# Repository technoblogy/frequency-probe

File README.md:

# Frequency Probe
A handheld tool that gives a visual indication of the frequency or voltage at the probe. See http://www.technoblogy.com/show?25C4

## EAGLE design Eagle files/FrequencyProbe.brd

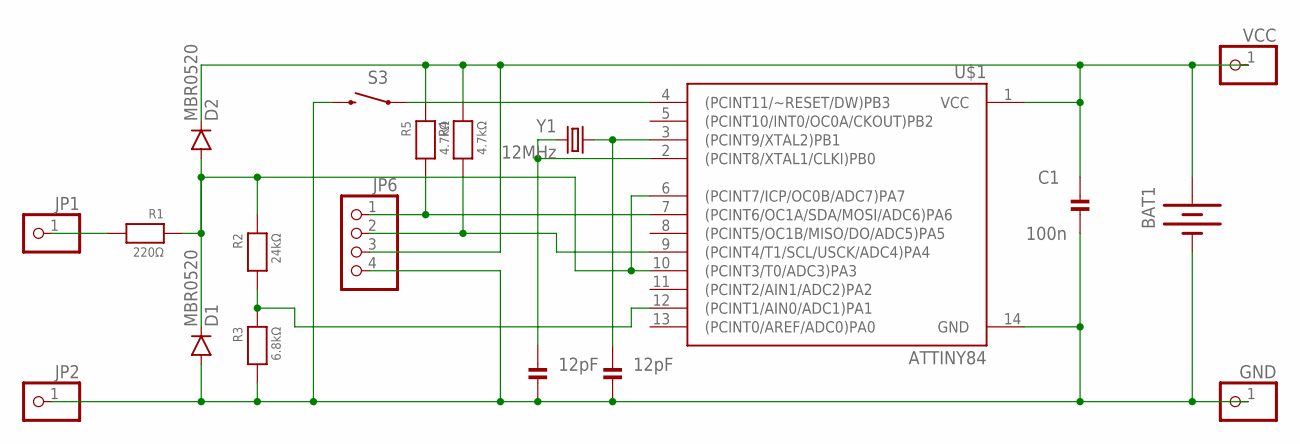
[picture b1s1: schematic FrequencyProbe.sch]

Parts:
BAT1: BATTERY12MM; BATTCON_12MM
C1: 100n; _0805MP
C12, C13: 12pF; _0805MP
D1, D2: MBR0520; SOD-123
GND: PINHD-1X1CB; 1X01-CLEANBIG
JP1, JP2: PINHD-1X1CB; 1X01-CLEANBIG
JP6: HEADER-1X4ROUND; 1X04_ROUND
R1: 220Ω; _0805MP
R2: 24kΩ; _0805MP
R3: 6.8kΩ; _0805MP
R4, R5: 4.7kΩ; _0805MP
S3: SWITCH-MOMENTARY-2SMD; TACTILE-SWITCH-SMD
U$1: ATTINY84; SO14
VCC: PINHD-1X1CB; 1X01-CLEANBIG
Y1: 12MHz; CRYSTAL-SMD-5X3

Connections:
GND: BAT1.GND (-), C1.2, C12.2, C13.2, D1.A, GND.1, JP2.1, JP6.4, R3.2, S3.3 (2), U$1.14 (GND)
unnamed: JP6.2, R4.2, U$1.9 ((PCINT4/T1/SCL/USCK/ADC4)PA4)
unnamed: JP6.1, R5.2, U$1.7 ((PCINT6/OC1A/SDA/MOSI/ADC6)PA6)
unnamed: D1.C, D2.A, R1.1, R2.1, U$1.6 ((PCINT7/ICP/OC0B/ADC7)PA7), U$1.10 ((PCINT3/T0/ADC3)PA3)
unnamed: C12.1, U$1.3 ((PCINT9/XTAL2)PB1), Y1.1
unnamed: S3.1, U$1.4 ((PCINT11/~RESET/DW)PB3)
unnamed: C13.1, U$1.2 ((PCINT8/XTAL1/CLKI)PB0), Y1.3 (2)
unnamed: R2.2, R3.1, U$1.12 ((PCINT1/AIN0/ADC1)PA1)
unnamed: JP1.1, R1.2
VCC: BAT1.PWR@1 (+), C1.1, D2.C, JP6.3, R4.1, R5.1, U$1.1 (VCC), VCC.1

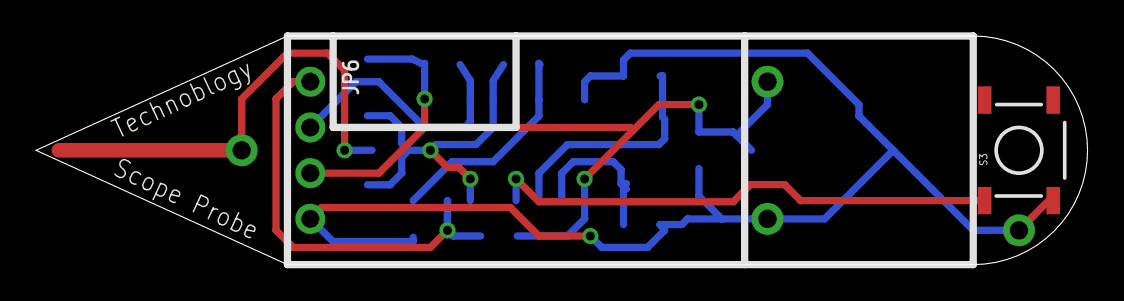
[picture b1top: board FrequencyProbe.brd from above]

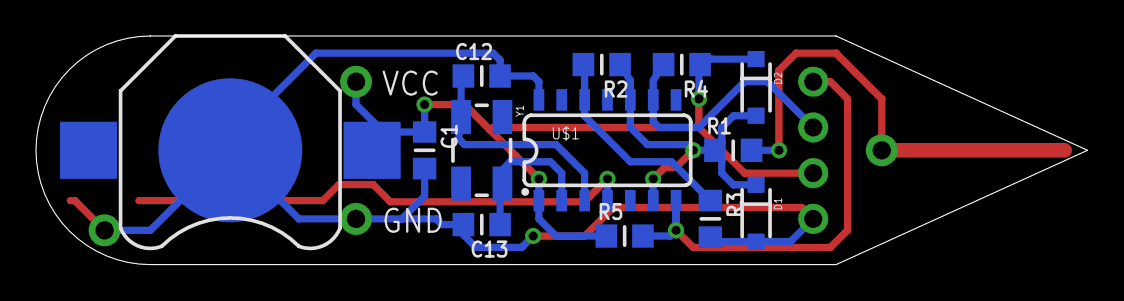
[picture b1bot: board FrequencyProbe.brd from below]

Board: 2 copper layers, 58.4 x 12.7 mm, 19 parts (13 on the bottom side), 10 nets.

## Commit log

2020-12-07 Version 1 - 7th December 2020

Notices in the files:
parts and their libraries:
SparkFun-DigitalIC: Licensing: Creative Commons ShareAlike 4.0 International - https://creativecommons.org/licenses/by-sa/4.0
microbuilder: This work is placed in the public domain, and may be freely used for commercial and non-commercial work with the following conditions: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
